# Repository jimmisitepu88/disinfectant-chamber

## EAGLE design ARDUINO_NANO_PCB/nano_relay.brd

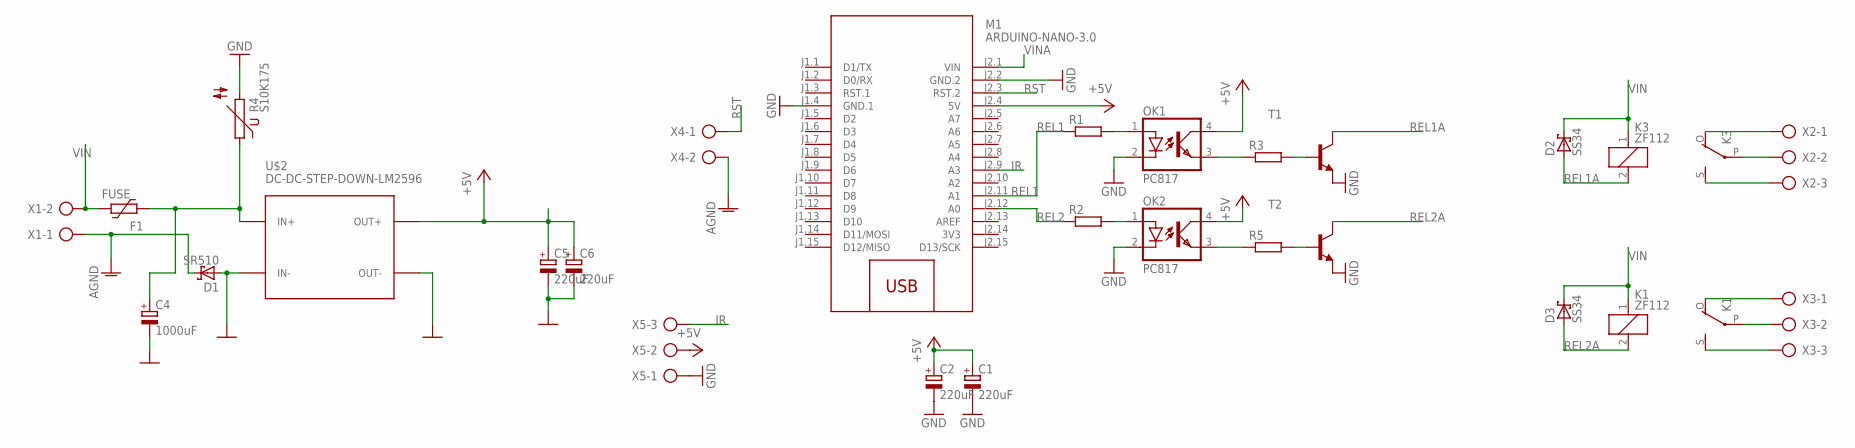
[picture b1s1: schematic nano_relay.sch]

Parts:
C1, C2, C5, C6: 220uF; E2,5-7
C4: 1000uF; E5-8,5
D1: SR510; SMB
D2, D3: SS34; SMB
F1: FUSE; 1812L
K1, K3: ZF112
M1: ARDUINO-NANO-3.0
OK1, OK2: PC817; DIL04
R1, R2, R3, R5: R-EU_M0805; M0805
R4: S10K175
T1, T2: MMBT2222ALT1-NPN-SOT23-BEC; SOT23-BEC
U$2: DC-DC-STEP-DOWN-LM2596
X1, X4: AK300/2
X2, X3, X5: AK300/3

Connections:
3V3: M1.J2.14 (3V3)
+5V: C1.+, C2.+, C5.+, C6.+, M1.J2.4 (5V), OK1.4 (COL), OK2.4 (COL), U$2.OUT+, X5.2
AGND: D1.C, X1.1, X4.2
GND: C1.-, C2.-, C4.-, C5.-, C6.-, D1.A, M1.J1.4 (GND.1), M1.J2.2 (GND.2), OK1.2 (C), OK2.2 (C), R4.2, T1.E, T2.E, U$2.IN-, U$2.OUT-, X5.1
IR: M1.J2.9 (A3), X5.3
unnamed: OK1.1 (A), R1.2
unnamed: OK2.1 (A), R2.2
unnamed: K3.P, X2.2
unnamed: C4.+, F1.2, R4.1, U$2.IN+
unnamed: K1.P, X3.2
unnamed: K1.O, X3.1
unnamed: K1.S, X3.3
unnamed: OK1.3 (EMIT), R3.1
unnamed: OK2.3 (EMIT), R5.1
unnamed: R3.2, T1.B
unnamed: R5.2, T2.B
unnamed: K3.O, X2.1
unnamed: K3.S, X2.3
REL1: M1.J2.11 (A1), R1.1
REL1A: D2.A, K3.2, T1.C
REL2: M1.J2.12 (A0), R2.1
REL2A: D3.A, K1.2, T2.C
RST: M1.J2.3 (RST.2), X4.1
VIN: D2.C, D3.C, F1.1, K1.1, K3.1, X1.2
VINA: M1.J2.1 (VIN)

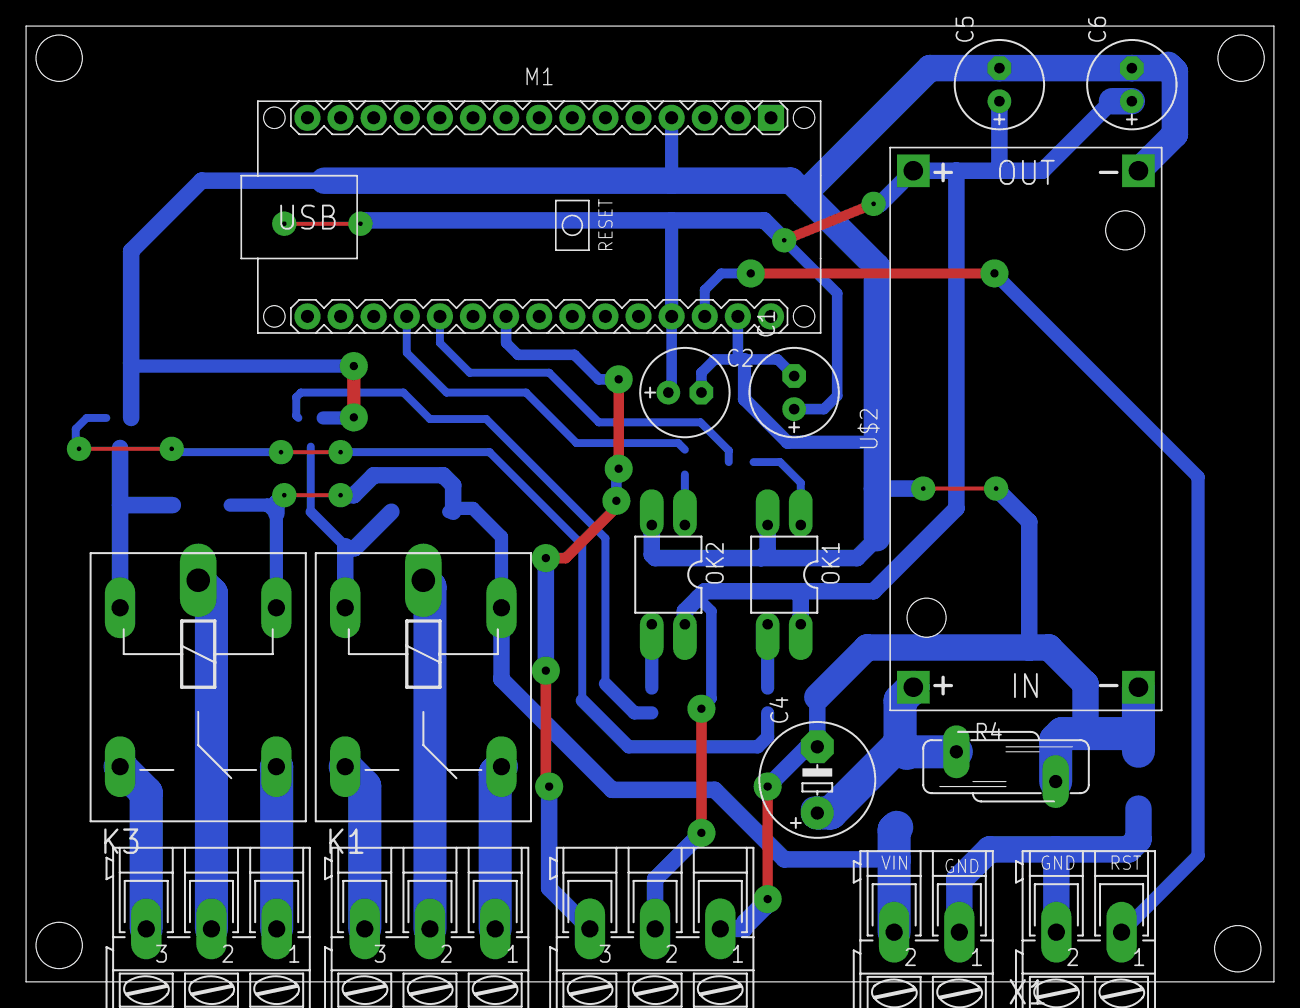
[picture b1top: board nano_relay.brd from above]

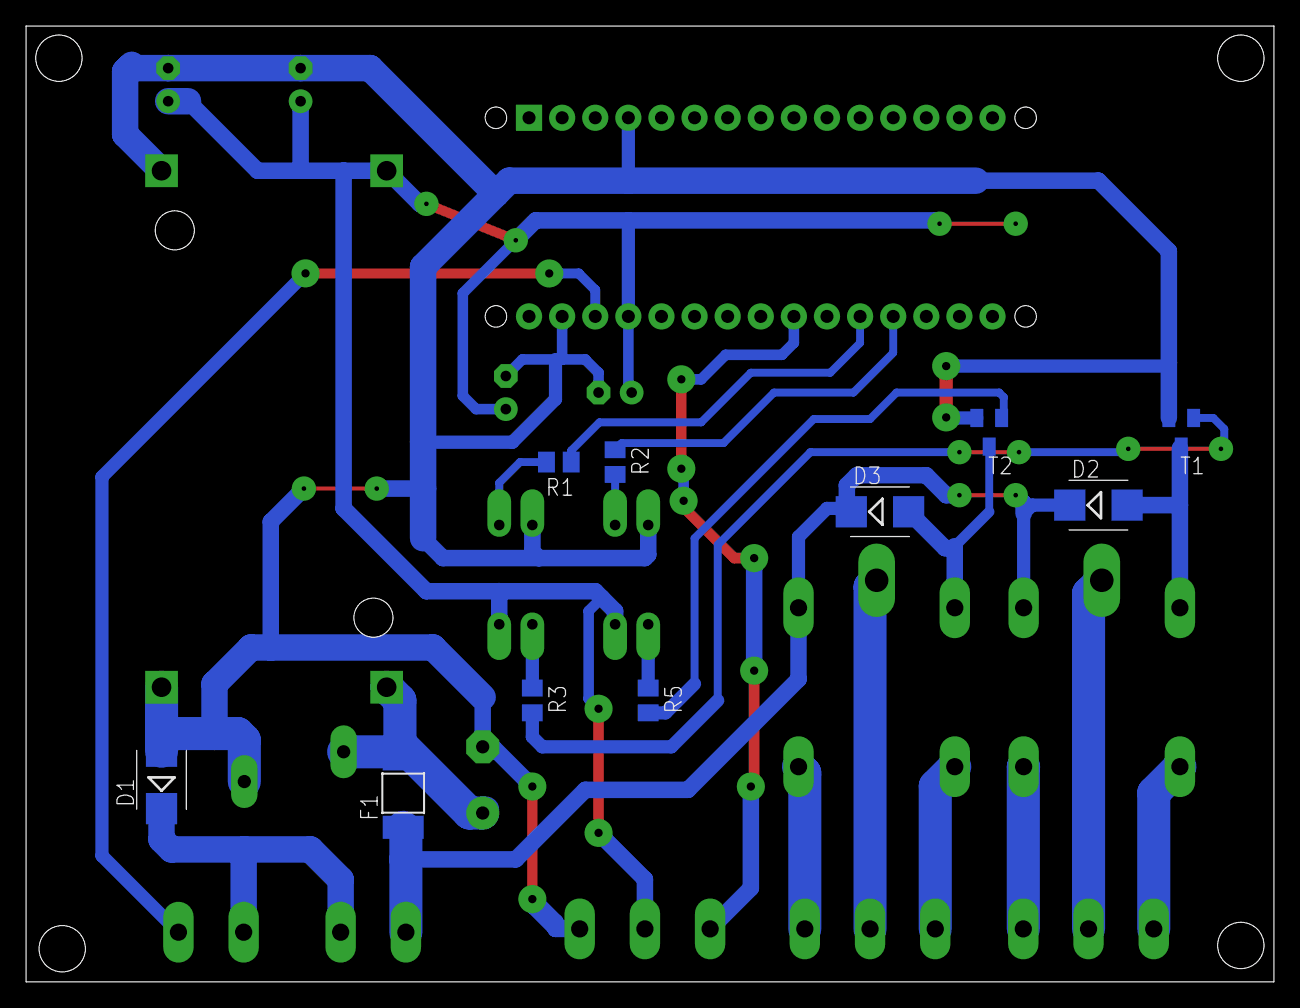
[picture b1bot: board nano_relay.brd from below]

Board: 2 copper layers, 95.7 x 73.3 mm, 27 parts (10 on the bottom side), 23 nets.

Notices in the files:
parts and their libraries:
diy-modules: Released under the Creative Commons Attribution 4.0 International License: http://creativecommons.org/licenses/by/4.0
